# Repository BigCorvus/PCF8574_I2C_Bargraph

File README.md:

# PCF8574_I2C_Bargraph
A small LED bar graph using the PCF8574 I2C port expander (TSSOP package)

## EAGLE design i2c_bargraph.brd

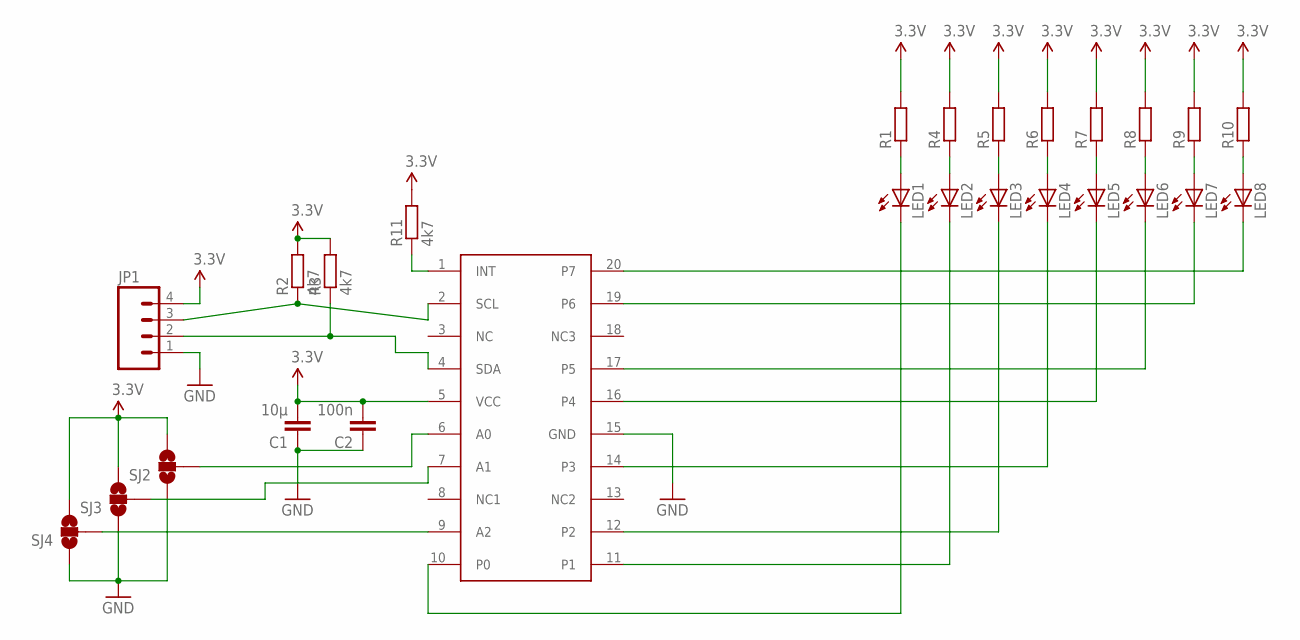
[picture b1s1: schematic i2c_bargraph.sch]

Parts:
C1: 10µ; C0603
C2: 100n; C0603
JP1: M04PTH; 1X04
LED1, LED2, LED3, LED4, LED5, LED6, LED7, LED8: LEDCHIP-LED0805; CHIP-LED0805
R1, R4, R5, R6, R7, R8, R9, R10: R-EU_R0603; R0603
R2, R3, R11: 4k7; R0603
SJ2, SJ3, SJ4: SOLDERJUMPER_2WAY-OLDS; SJ_3
U$1: PCF8574TSSOP; TSSOP20

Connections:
3.3V: C1.2, C2.2, JP1.4, R1.2, R2.2, R3.2, R4.2, R5.2, R6.2, R7.2, R8.2, R9.2, R10.2, R11.2, SJ2.3, SJ3.3, SJ4.3, U$1.5 (VCC)
GND: C1.1, C2.1, JP1.1, SJ2.1, SJ3.1, SJ4.1, U$1.15 (GND)
unnamed: JP1.3, R2.1, U$1.2 (SCL)
unnamed: JP1.2, R3.1, U$1.4 (SDA)
unnamed: R11.1, U$1.1 (INT)
unnamed: LED1.A, R1.1
unnamed: LED2.A, R4.1
unnamed: LED3.A, R5.1
unnamed: LED4.A, R6.1
unnamed: LED5.A, R7.1
unnamed: LED6.A, R8.1
unnamed: LED7.A, R9.1
unnamed: LED8.A, R10.1
unnamed: LED1.C, U$1.10 (P0)
unnamed: LED2.C, U$1.11 (P1)
unnamed: LED3.C, U$1.12 (P2)
unnamed: LED4.C, U$1.14 (P3)
unnamed: LED5.C, U$1.16 (P4)
unnamed: LED6.C, U$1.17 (P5)
unnamed: LED7.C, U$1.19 (P6)
unnamed: LED8.C, U$1.20 (P7)
unnamed: SJ4.2, U$1.9 (A2)
unnamed: SJ3.2, U$1.7 (A1)
unnamed: SJ2.2, U$1.6 (A0)

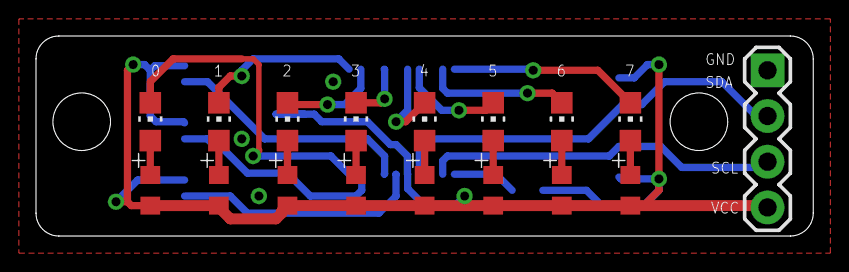
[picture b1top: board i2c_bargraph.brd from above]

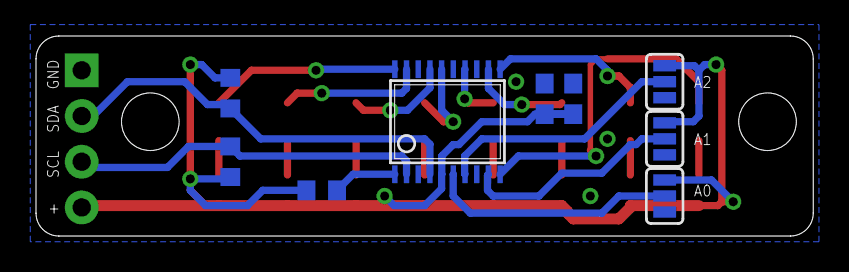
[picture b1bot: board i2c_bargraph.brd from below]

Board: 2 copper layers, 43.2 x 11.1 mm, 26 parts (9 on the bottom side), 24 nets.

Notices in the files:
parts and their libraries:
SparkFun-Connectors: Licensing: Creative Commons ShareAlike 4.0 International - https://creativecommons.org/licenses/by-sa/4.0
